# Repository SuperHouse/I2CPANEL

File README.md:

SuperHouse I2C Panel
====================
Copyright 2019 SuperHouse Automation Pty Ltd  www.superhouse.tv  

Navigation buttons and OLED screen for fitting in a rack mount case.

Features:

 * I2C interface to buttons and spare I/O headers
 * 128x64 I2C OLED screen

You can view more details at:

  http://www.superhouse.tv/i2cpanel

INSTALLATION
------------
The design is saved as an EAGLE project. EAGLE PCB design software is
available from www.cadsoftusa.com free for non-commercial use. To use
this project download it and place the directory containing these files
into the "eagle" directory on your computer. Then open EAGLE and
navigate to the project.

CREDITS
-------
Jonathan Oxer jon@oxer.com.au

DISTRIBUTION
------------
The specific terms of distribution of this project are governed by the
license referenced below.

LICENSE
-------
Licensed under the TAPR Open Hardware License (www.tapr.org/OHL).
The "license" folder within this repository also contains a copy of
this license in plain text format.

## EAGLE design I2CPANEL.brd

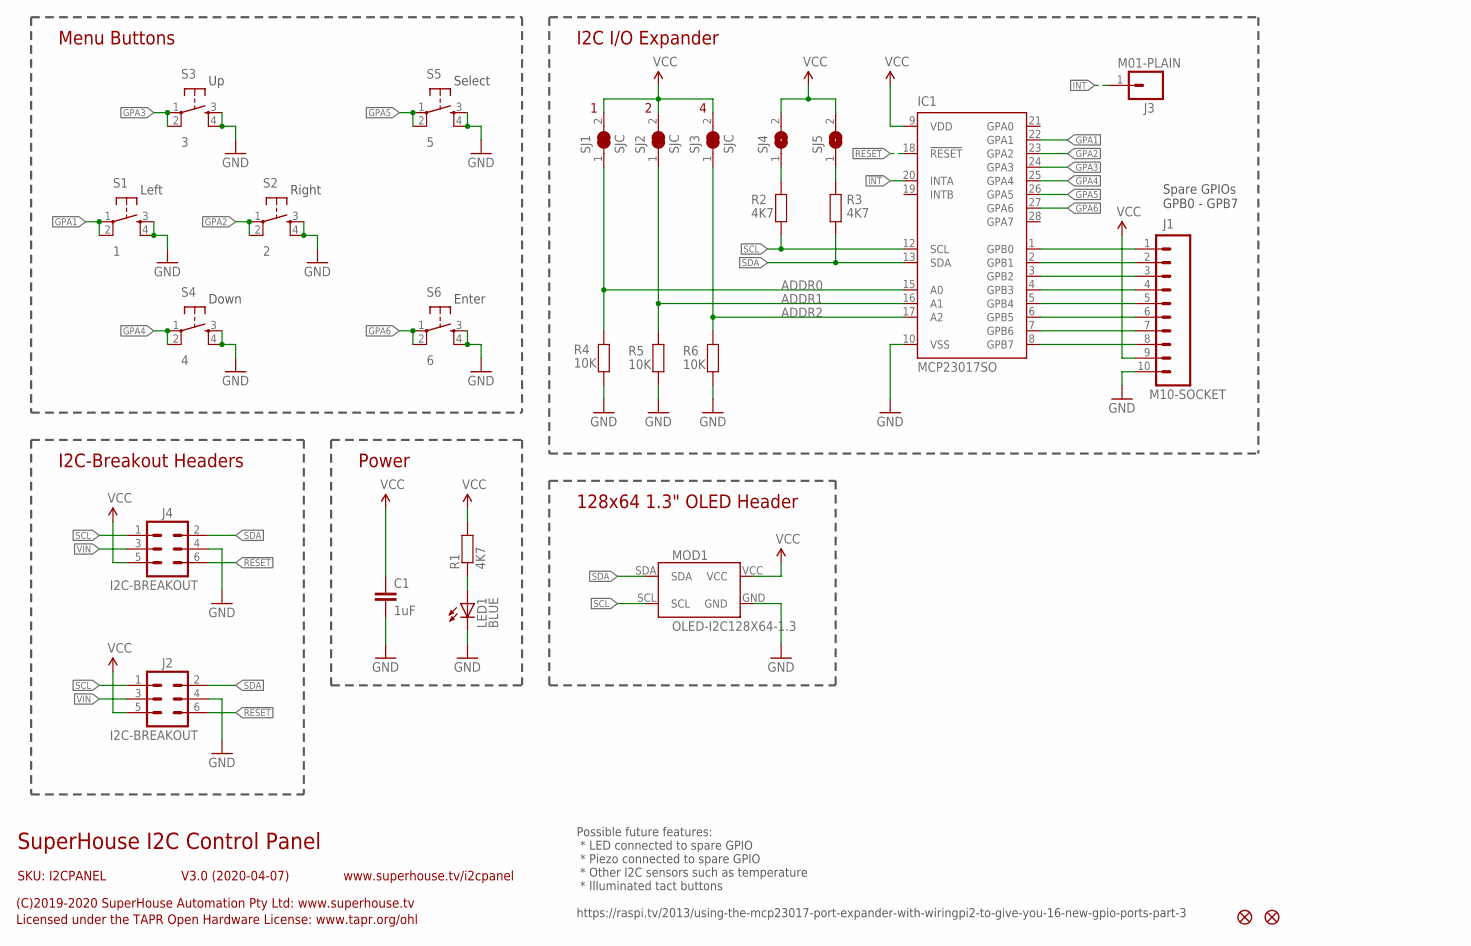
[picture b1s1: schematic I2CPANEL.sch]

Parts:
C1: 1uF; C0603
FID1, FID2: FIDUCIAL1X2.5; FIDUCIAL-1X2.5
IC1: MCP23017SO; SO28W
J1: M10-SOCKET; 1X10-S
J2, J4: I2C-BREAKOUT; 2X03-SHROUDED
J3: M01-PLAIN; 1X01
LED1: BLUE; LED-0603
MOD1: OLED-I2C128X64-1.3; OLED-128X64-1.3
R1, R2, R3: 4K7; R0603
R4, R5, R6: 10K; R0603
S1: 1; TACTILE-PTH-6MM
S2: 2; TACTILE-PTH-6MM
S3: 3; TACTILE-PTH-6MM
S4: 4; TACTILE-PTH-6MM
S5: 5; TACTILE-PTH-6MM
S6: 6; TACTILE-PTH-6MM
SJ1, SJ2, SJ3: SJC
SJ4, SJ5: SJN; SJ

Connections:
!INT: IC1.20 (INTA), J3.1
!RESET: IC1.18 (!RESET), J2.6, J4.6
ADDR0: IC1.15 (A0), R4.2, SJ1.1
ADDR1: IC1.16 (A1), R5.2, SJ2.1
ADDR2: IC1.17 (A2), R6.2, SJ3.1
GND: C1.2, IC1.10 (VSS), J1.10, J2.4, J4.4, LED1.C, MOD1.GND, R4.1, R5.1, R6.1, S1.3, S1.4, S2.3, S2.4, S3.3, S3.4, S4.3, S4.4, S5.3, S5.4, S6.3, S6.4
GPA1: IC1.22 (GPA1), S1.1, S1.2
GPA2: IC1.23 (GPA2), S2.1, S2.2
GPA3: IC1.24 (GPA3), S3.1, S3.2
GPA4: IC1.25 (GPA4), S4.1, S4.2
GPA5: IC1.26 (GPA5), S5.1, S5.2
GPA6: IC1.27 (GPA6), S6.1, S6.2
unnamed: IC1.1 (GPB0), J1.1
unnamed: IC1.2 (GPB1), J1.2
unnamed: IC1.3 (GPB2), J1.3
unnamed: IC1.4 (GPB3), J1.4
unnamed: IC1.5 (GPB4), J1.5
unnamed: LED1.A, R1.1
unnamed: IC1.6 (GPB5), J1.6
unnamed: IC1.7 (GPB6), J1.7
unnamed: IC1.8 (GPB7), J1.8
unnamed: R2.2, SJ4.1
unnamed: R3.2, SJ5.1
SCL: IC1.12 (SCL), J2.1, J4.1, MOD1.SCL, R2.1
SDA: IC1.13 (SDA), J2.2, J4.2, MOD1.SDA, R3.1
VCC: C1.1, IC1.9 (VDD), J1.9, J2.5, J4.5, MOD1.VCC, R1.2, SJ1.2, SJ2.2, SJ3.2, SJ4.2, SJ5.2
VIN: J2.3, J4.3

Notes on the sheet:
SuperHouse I2C Control Panel
V3.0 (2020-04-07)
SKU: I2CPANEL
(C)2019-2020 SuperHouse Automation Pty Ltd: www.superhouse.tv
Licensed under the TAPR Open Hardware License: www.tapr.org/ohl
www.superhouse.tv/i2cpanel
Power
Menu Buttons
128x64 1.3" OLED Header
Possible future features: * LED connected to spare GPIO * Piezo connected to spare GPIO * Other I2C sensors such as temperature * Illuminated tact buttons https://raspi.tv/2013/using-the-mcp23017-port-expander-with-wiringpi2-to-give-you-16-new-gpio-ports-part-3
I2C-Breakout Headers
Spare GPIOs GPB0 - GPB7
I2C I/O Expander
Down
Left
Right
Select
Enter

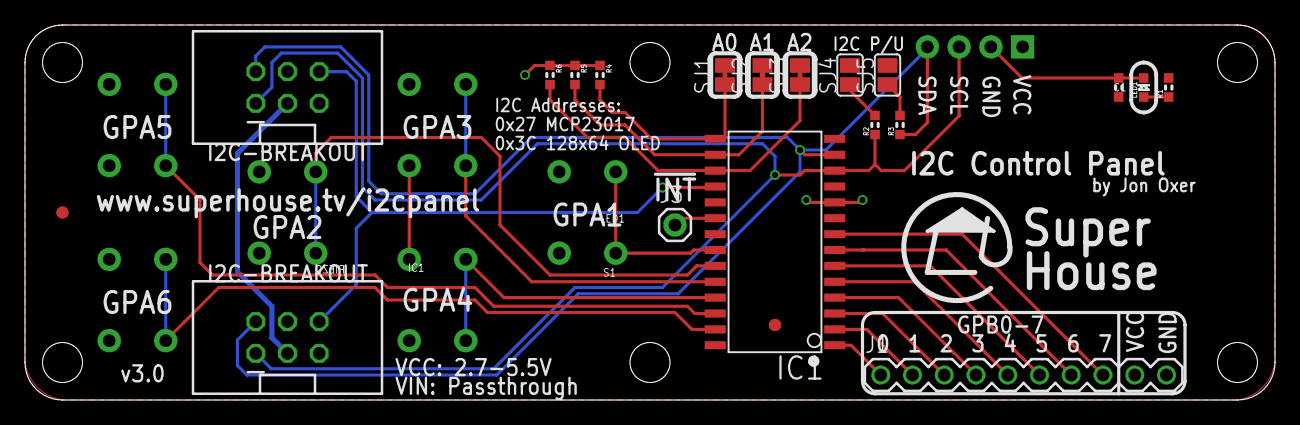
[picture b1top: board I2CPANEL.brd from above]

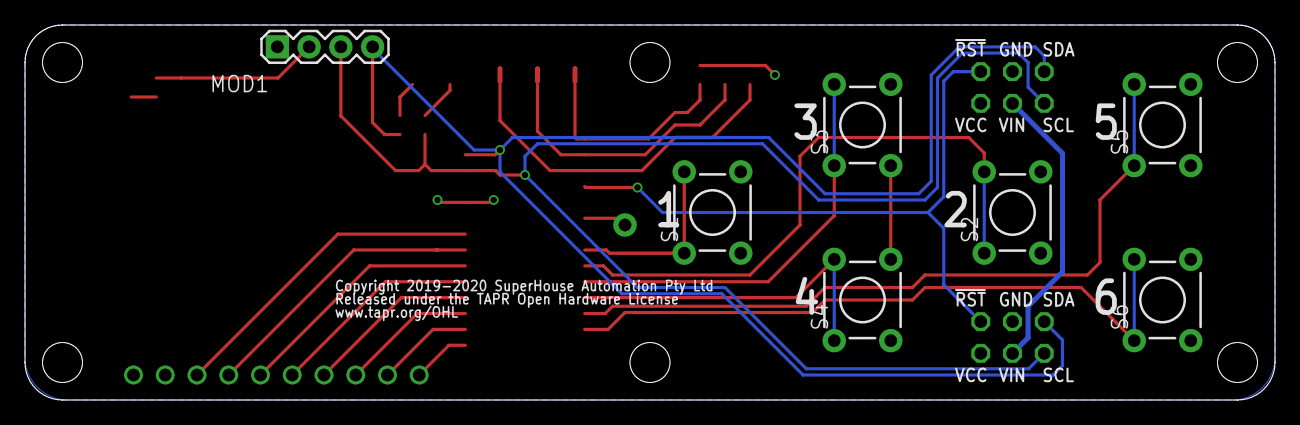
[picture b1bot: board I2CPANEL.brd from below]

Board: 2 copper layers, 100.0 x 30.0 mm, 27 parts (7 on the bottom side), 27 nets.

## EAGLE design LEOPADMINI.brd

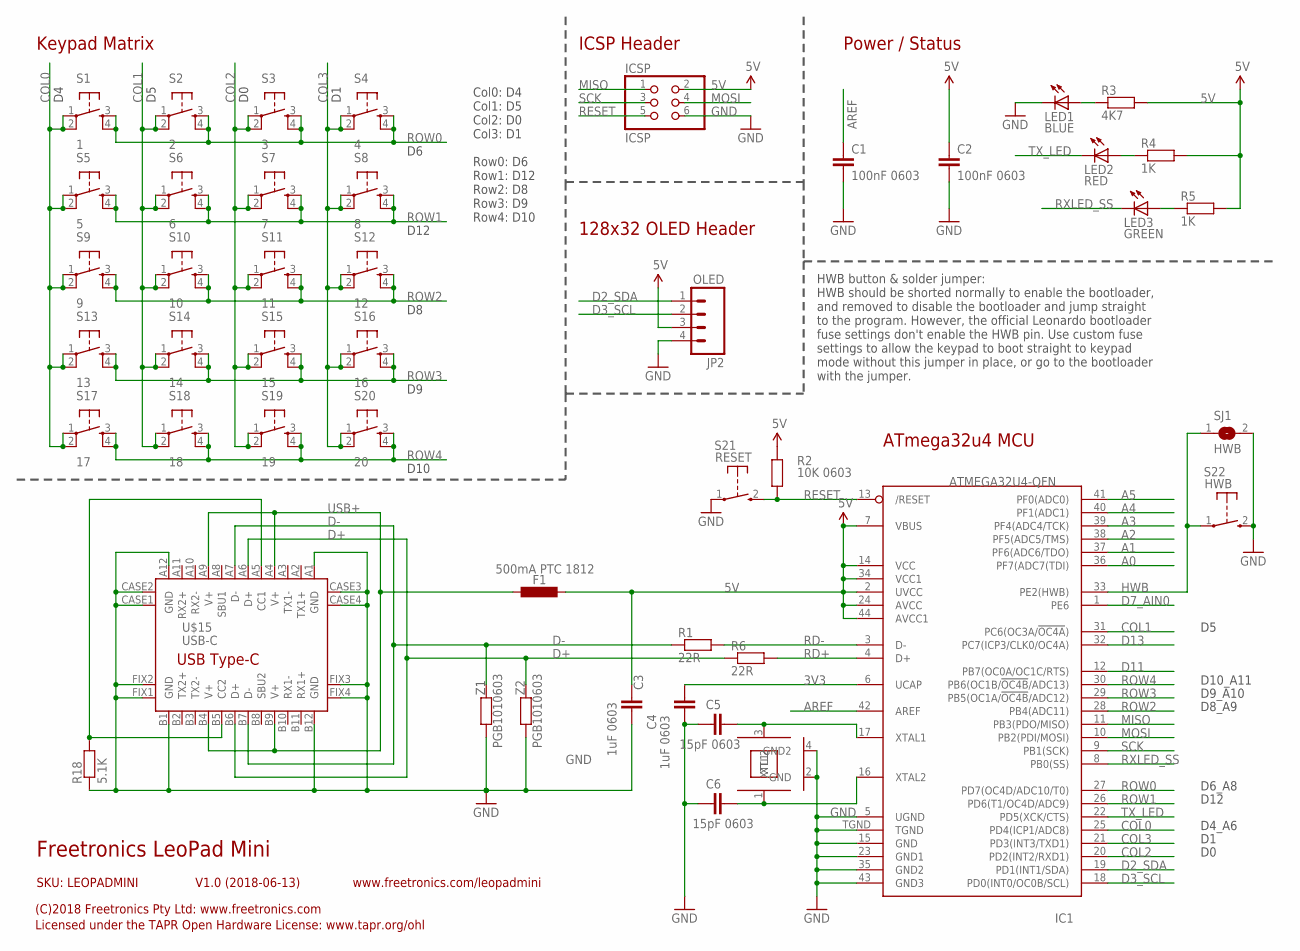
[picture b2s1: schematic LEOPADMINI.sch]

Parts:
C1, C2: 100nF 0603; 0603
C3, C4: 1uF 0603; 0603
C5, C6: 15pF 0603; 0603
F1: 500mA PTC 1812; L1812
IC1: ATMEGA32U4-QFN; QFN-44N
ICSP: ICSP; 2X03
JP2: OLED; 1X04
LED1: BLUE; LED-0603
LED2: RED; LED-0603
LED3: GREEN; LED-0603
R1, R6: 22R; 0603
R2: 10K 0603; 0603
R3: 4K7; 0603
R4, R5: 1K; 0603
R18: 5.1K; 0603
S1: 1; TACTILE-PTH-4.5MM
S2: 2; TACTILE-PTH-4.5MM
S3: 3; TACTILE-PTH-4.5MM
S4: 4; TACTILE-PTH-4.5MM
S5: 5; TACTILE-PTH-4.5MM
S6: 6; TACTILE-PTH-4.5MM
S7: 7; TACTILE-PTH-4.5MM
S8: 8; TACTILE-PTH-4.5MM
S9: 9; TACTILE-PTH-4.5MM
S10: 10; TACTILE-PTH-4.5MM
S11: 11; TACTILE-PTH-4.5MM
S12: 12; TACTILE-PTH-4.5MM
S13: 13; TACTILE-PTH-4.5MM
S14: 14; TACTILE-PTH-4.5MM
S15: 15; TACTILE-PTH-4.5MM
S16: 16; TACTILE-PTH-4.5MM
S17: 17; TACTILE-PTH-4.5MM
S18: 18; TACTILE-PTH-4.5MM
S19: 19; TACTILE-PTH-4.5MM
S20: 20; TACTILE-PTH-4.5MM
S21: RESET; TACTILE_SWITCH_SMD_2PIN_TINY
S22: HWB; TACTILE_SWITCH_SMD_2PIN_TINY
SJ1: HWB; SJ
U$15: USB-C; USB-C-U52A
XTL1: 16MHz; CRYSTAL-SMD-3X2
Z1, Z2: PGB1010603; 0603

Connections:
3V3: C4.2, IC1.6 (UCAP)
5V: C2.1, C3.1, F1.2, IC1.2 (UVCC), IC1.7 (VBUS), IC1.14 (VCC), IC1.24 (AVCC), IC1.34 (VCC1), IC1.44 (AVCC1), ICSP.2, JP2.3, R2.2, R3.2, R4.2, R5.2
A0: IC1.36 (PF7(ADC7(TDI))
A1: IC1.37 (PF6(ADC6/TDO))
A2: IC1.38 (PF5(ADC5/TMS))
A3: IC1.39 (PF4(ADC4/TCK))
A4: IC1.40 (PF1(ADC1))
A5: IC1.41 (PF0(ADC0))
AREF: C1.1, IC1.42 (AREF)
COL0: IC1.25 (PD4(ICP1/ADC8)), S1.1, S1.2, S5.1, S5.2, S9.1, S9.2, S13.1, S13.2, S17.1, S17.2
COL1: IC1.31 (PC6(OC3A/!OC4A!)), S2.1, S2.2, S6.1, S6.2, S10.1, S10.2, S14.1, S14.2, S18.1, S18.2
COL2: IC1.20 (PD2(INT2/RXD1)), S3.1, S3.2, S7.1, S7.2, S11.1, S11.2, S15.1, S15.2, S19.1, S19.2
COL3: IC1.21 (PD3(INT3/TXD1)), S4.1, S4.2, S8.1, S8.2, S12.1, S12.2, S16.1, S16.2, S20.1, S20.2
D2_SDA: IC1.19 (PD1(INT1/SDA)), JP2.1
D3_SCL: IC1.18 (PD0(INT0/OC0B/SCL)), JP2.2
D7_AIN0: IC1.1 (PE6)
D11: IC1.12 (PB7(OC0A/OC1C/RTS))
D13: IC1.32 (PC7(ICP3/CLK0/OC4A))
D+: R6.1, U$15.A6 (D+), U$15.B6 (D+), Z2.2
D-: R1.1, U$15.A7 (D-), U$15.B7 (D-), Z1.2
GND: C1.2, C2.2, C3.2, C4.1, C5.1, C6.1, IC1.5 (UGND), IC1.15 (GND), IC1.23 (GND1), IC1.35 (GND2), IC1.43 (GND3), IC1.TGND, ICSP.6, JP2.4, LED1.C, R18.1, S21.1, S22.2 (S), SJ1.2, U$15.A1 (GND), U$15.A12 (GND), U$15.B1 (GND), U$15.B12 (GND), U$15.CASE1 (GND), U$15.CASE2 (GND), U$15.CASE3 (GND), U$15.CASE4 (GND), U$15.FIX1 (GND), U$15.FIX2 (GND), U$15.FIX3 (GND), U$15.FIX4 (GND), XTL1.2 (GND), XTL1.4 (GND2), Z1.1, Z2.1
HWB: IC1.33 (PE2(HWB)), S22.1, SJ1.1
MISO: IC1.11 (PB3(PDO/MISO)), ICSP.1
MOSI: IC1.10 (PB2(PDI/MOSI)), ICSP.4
unnamed: LED1.A, R3.1
unnamed: LED2.A, R4.1
unnamed: LED3.A, R5.1
unnamed: C5.2, IC1.17 (XTAL1), XTL1.3 (XTL2)
unnamed: C6.2, IC1.16 (XTAL2), XTL1.1 (XTL1)
unnamed: R18.2, U$15.A5 (CC1), U$15.B5 (CC2)
RD+: IC1.4 (D+), R6.2
RD-: IC1.3 (D-), R1.2
RESET: IC1.13 (/RESET), ICSP.5, R2.1, S21.2 (S)
ROW0: IC1.27 (PD7(OC4D/ADC10/T0)), S1.3, S1.4, S2.3, S2.4, S3.3, S3.4, S4.3, S4.4
ROW1: IC1.26 (PD6(T1/OC4D/ADC9)), S5.3, S5.4, S6.3, S6.4, S7.3, S7.4, S8.3, S8.4
ROW2: IC1.28 (PB4(ADC11)), S9.3, S9.4, S10.3, S10.4, S11.3, S11.4, S12.3, S12.4
ROW3: IC1.29 (PB5(OC1A/!OC4B!/ADC12)), S13.3, S13.4, S14.3, S14.4, S15.3, S15.4, S16.3, S16.4
ROW4: IC1.30 (PB6(OC1B/!OC4B!/ADC13)), S17.3, S17.4, S18.3, S18.4, S19.3, S19.4, S20.3, S20.4
RXLED_SS: IC1.8 (PB0(SS)), LED3.C
SCK: IC1.9 (PB1(SCK)), ICSP.3
TX_LED: IC1.22 (PD5(XCK/CTS)), LED2.C
USB+: F1.1, U$15.A4 (V+), U$15.A9 (V+), U$15.B4 (V+), U$15.B9 (V+)

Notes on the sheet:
ICSP Header
ATmega32u4 MCU
HWB button & solder jumper: HWB should be shorted normally to enable the bootloader, and removed to disable the bootloader and jump straight to the program. However, the official Leonardo bootloader fuse settings don't enable the HWB pin. Use custom fuse settings to allow the keypad to boot straigh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
Freetronics LeoPad Mini
V1.0 (2018-06-13)
SKU: LEOPADMINI
(C)2018 Freetronics Pty Ltd: www.freetronics.com
Licensed under the TAPR Open Hardware License: www.tapr.org/ohl
www.freetronics.com/leopadmini
Power / Status
D10_A11
D9_A10
D8_A9
D6_A8
D12
Col0: D4 Col1: D5 Col2: D0 Col3: D1 Row0: D6 Row1: D12 Row2: D8 Row3: D9 Row4: D10
Keypad Matrix
D4_A6
128x32 OLED Header
D10

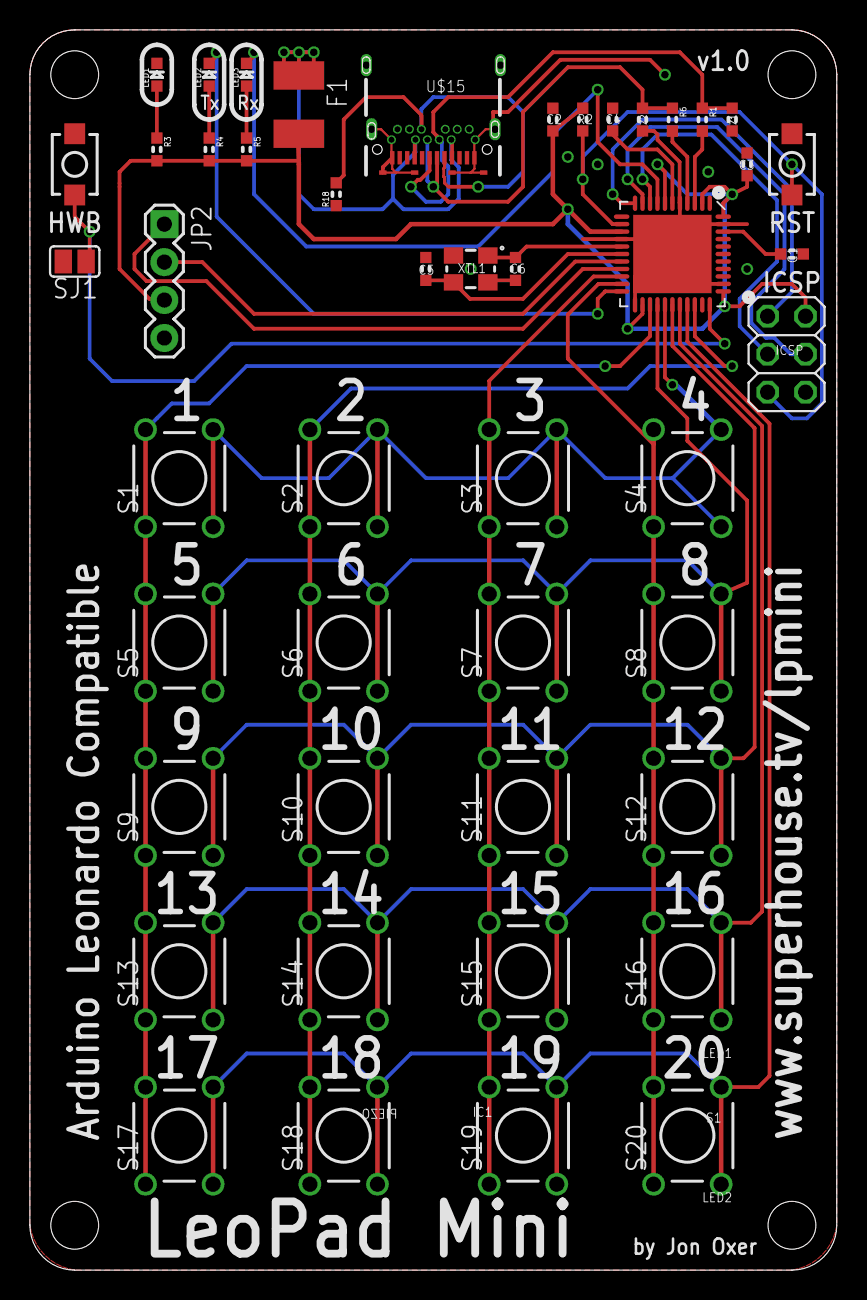
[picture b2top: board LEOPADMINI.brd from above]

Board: 2 copper layers, 54.0 x 83.0 mm, 47 parts (0 on the bottom side), 33 nets.

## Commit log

2018-07-14 Imported files from LeoPad project
2019-04-24 Resized to suit 6mm tact switches
2019-05-22 Migrated project files from LEOPADMINI
2019-05-22 Schematic and routing for v1.0 release
2019-05-23 Major rework to use 128x32 screen for v1.0 release
2019-05-23 Added mechanical dimensions
2019-07-01 3D models
2019-07-10 Added second OLED mount
2019-08-30 Routing with larger OLED for v2.0 release
2020-04-08 Changed to I2C-BREAKOUT header for v3.0 release
2020-04-30 Renumbered designators to simplify BOM

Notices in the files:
I2CPANEL.brd:
Copyright 2019-2020 SuperHouse Automation Pty Ltd
Released under the TAPR Open Hardware License
LEOPADMINI.brd:
Copyright 2018 SuperHouse Automation Pty Ltd
